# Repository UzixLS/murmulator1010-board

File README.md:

## Murmulator.1010
10×10 cm, 2-layer DIY computer PCB based on the Raspberry Pi RP2350 MCU

Technical specs:
- Compatible with the [Murmulator](https://murmulator.ru/) [M2P2](https://murmulator.ru/nextgen)
  and [Frank PGA](https://frank.rh1.tech/ru-ru/hardware/frank-pga) projects
- HDMI and VGA video outputs
- CVBS composite video + audio output via 3.5mm jack connector
- PWM and I2S (TDA1387T DAC) audio output with LMV358 opamp
- Combined PS/2 keyboard and mouse port
- Two DB-9 ports for Famicom (Dendy)-compatible joysticks
- Two external USB-host ports and two internal connectors via an MW7211A hub
- USB Type-C power supply and programming
- RP2350B MCU in a QFN-80 package
- 16MB SPI flash (W25Q128)
- Two PSRAM chips: SPI + QSPI
- RTC (DS3231MZ) with battery
- ESP8266 WiFi module (ESP-01 or ESP-12E/F)
- SD/microSD card slot
- Tape input via a second 3.5 mm jack
- ESD protection for PS/2, joystick, and USB Type-C ports
- 5V level shifters for PS/2 and joystick ports
- Board optimized for G738 and G706 cases

### Navigation
[release/pcb.rev.A1.pdf](https://uzixls.github.io/murmulator1010-board/release/pcb.rev.A1.pdf) - schematic, BOM and 3d renders  
[release/pcb.rev.A1.bom_interactive.html](https://uzixls.github.io/murmulator1010-board/release/pcb.rev.A1.bom_interactive.html) - interactive BOM  
[release/pcb.rev.A1.gerber.zip](https://uzixls.github.io/murmulator1010-board/release/pcb.rev.A1.gerber.zip) - gerber files  
[release/pcb_covers.rev.A1.gerber.zip](https://uzixls.github.io/murmulator1010-board/release/pcb_covers.rev.A1.gerber.zip) - gerber files for covers  

### Changelog
#### Main PCB
* Rev.A - initial release
* Rev.A1:
    - U6 marked as DNP
    - Minor silkscreen improvements

#### Covers PCB
* Rev.A - initial release
* Rev.A1:
    - HDMI and USB cutouts moved down by 0.25mm
    - PS/2 cutout moved up by 0.25mm

### MCU pinout
| GPIO | Function |
| ---- | -------- |
| GP0  | PS/2 mouse clock |
| GP1  | PS/2 mouse data |
| GP2  | PS/2 keyboard clock |
| GP3  | PS/2 keyboard data |
| GP4  | SPI SD card and PSRAM MISO |
| GP5  | SPI SD card select |
| GP6  | SPI SD card and PSRAM clock |
| GP7  | SPI SD card and PSRAM MOSI |
| GP8  | SPI PSRAM select |
| GP9  | I2S data / PWM beeper |
| GP10 | I2S clock / PWM R |
| GP11 | I2S LR clock / PWM L |
| GP12 | HDMI CKN / VGA B bit 0 / CVBS bit 0 |
| GP13 | HDMI CKP / VGA B bit 1 / CVBS bit 1 |
| GP14 | HDMI D0N / VGA G bit 0 / CVBS bit 4 |
| GP15 | HDMI D0P / VGA G bit 1 / CVBS bit 5 |
| GP16 | HDMI D1N / VGA R bit 0 / CVBS bit 2 |
| GP17 | HDMI D1P / VGA R bit 1 / CVBS bit 3 |
| GP18 | HDMI D2N / VGA horizontal sync / CVBS bit 6 |
| GP19 | HDMI D2P / VGA vertical sync |
| GP20 | NES joystick 1+2 clock |
| GP21 | NES joystick 1+2 latch |
| GP22 | Tape input |
| GP23 | — |
| GP24 | User button |
| GP25 | User LED |
| GP26 | NES joystick 1 data |
| GP27 | NES joystick 2 data |
| GP28 | RTC I2C SDA |
| GP29 | RTC I2C SCL |
| GP30 | — |
| GP31 | Test point TP4 |
| GP32 | Test point TP5 |
| GP33 | Test point TP6 |
| GP34 | — |
| GP35 | — |
| GP36 | — |
| GP37 | — |
| GP38 | ESP UART RX (MCU output) |
| GP39 | ESP UART TX (MCU input) |
| GP40 | — |
| GP41 | — |
| GP42 | — |
| GP43 | — |
| GP44 | — |
| GP45 | — |
| GP46 | Test point TP7 |
| GP47 | QSPI PSRAM select |

### References
* Murmulator official site: [link](https://murmulator.ru/)
* Murmulator 2 pinout and firmware: [link](https://murmulator.ru/nextgen)
* Frank PGA: [link](https://frank.rh1.tech/ru-ru/hardware/frank-pga)

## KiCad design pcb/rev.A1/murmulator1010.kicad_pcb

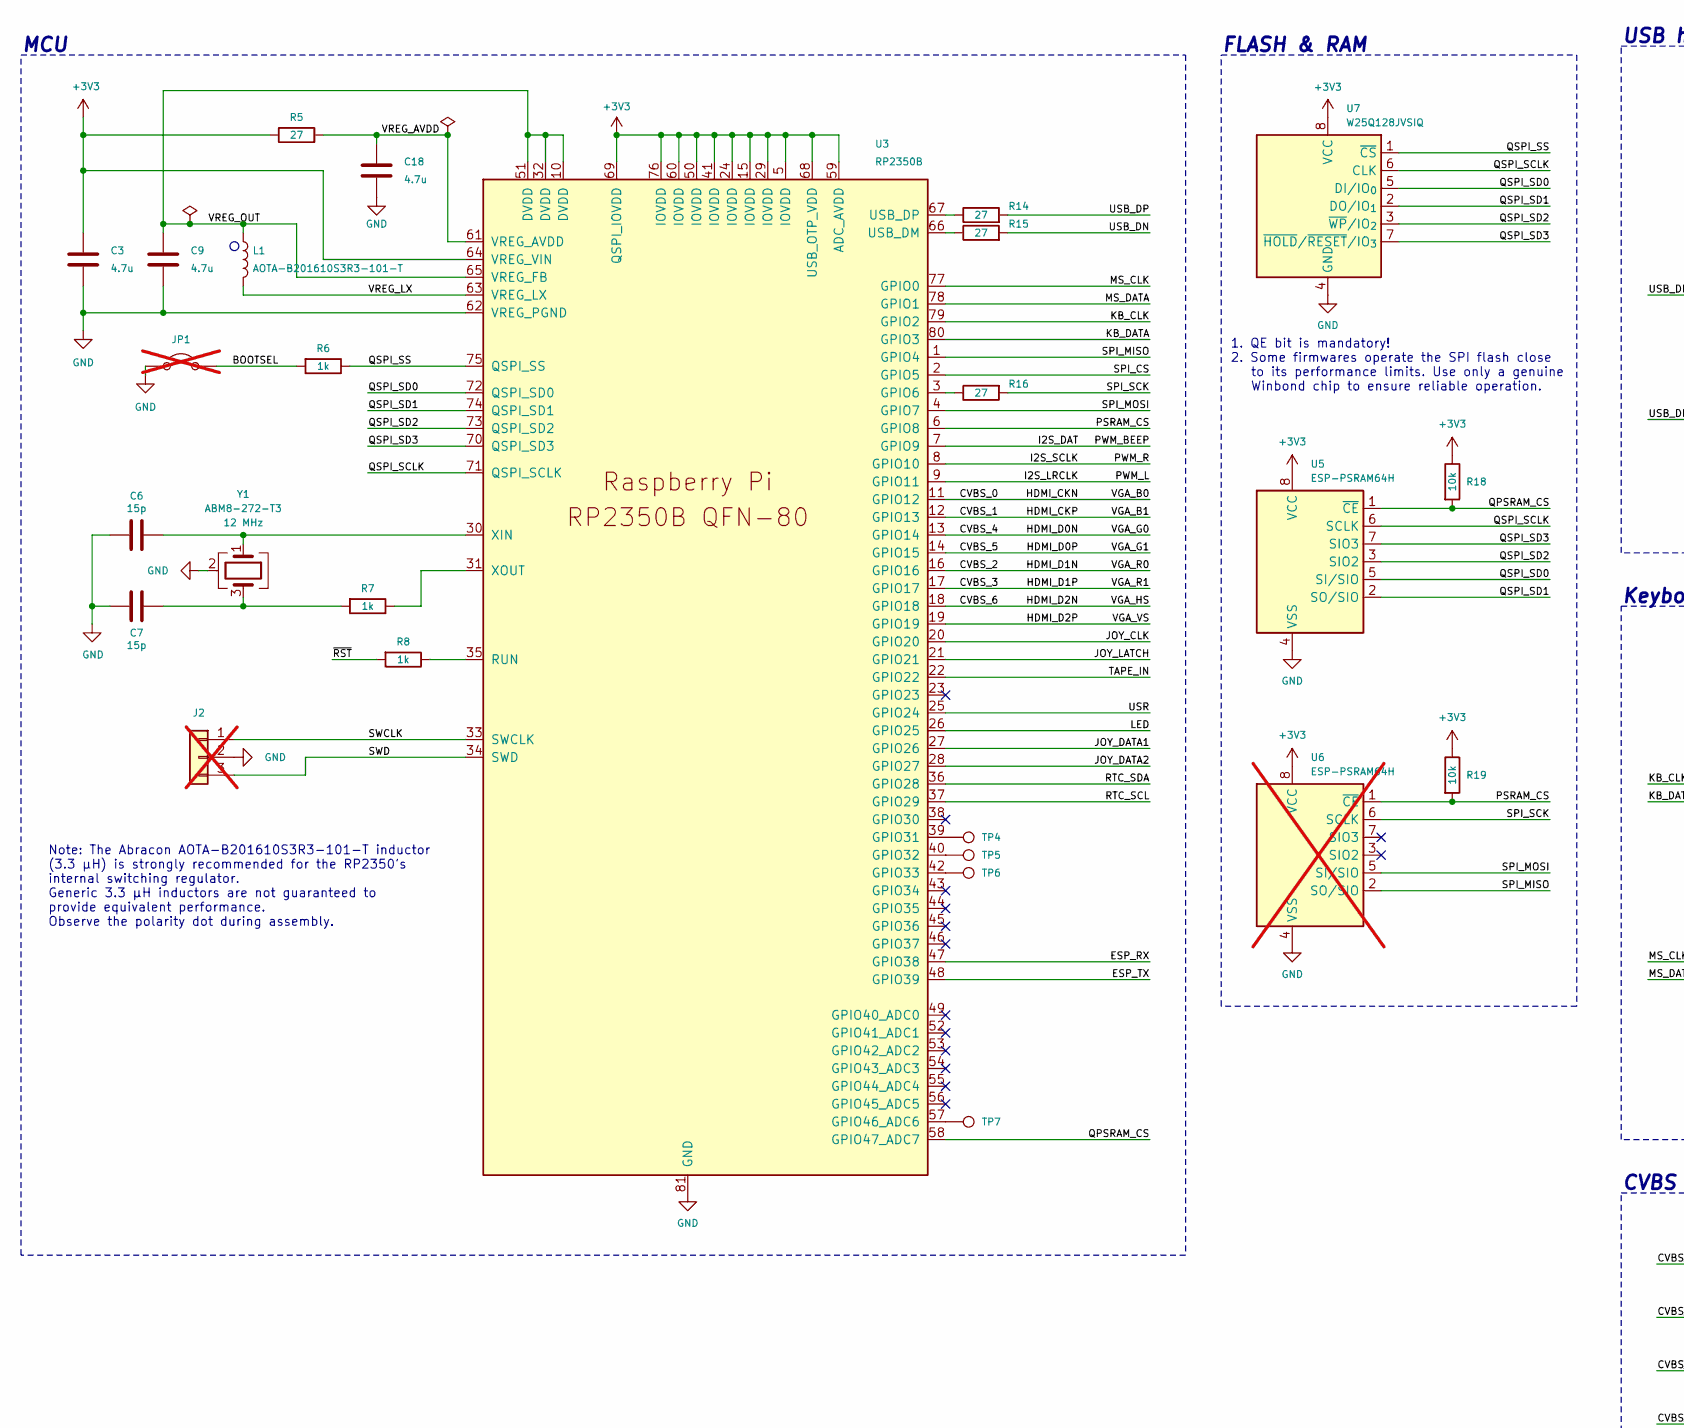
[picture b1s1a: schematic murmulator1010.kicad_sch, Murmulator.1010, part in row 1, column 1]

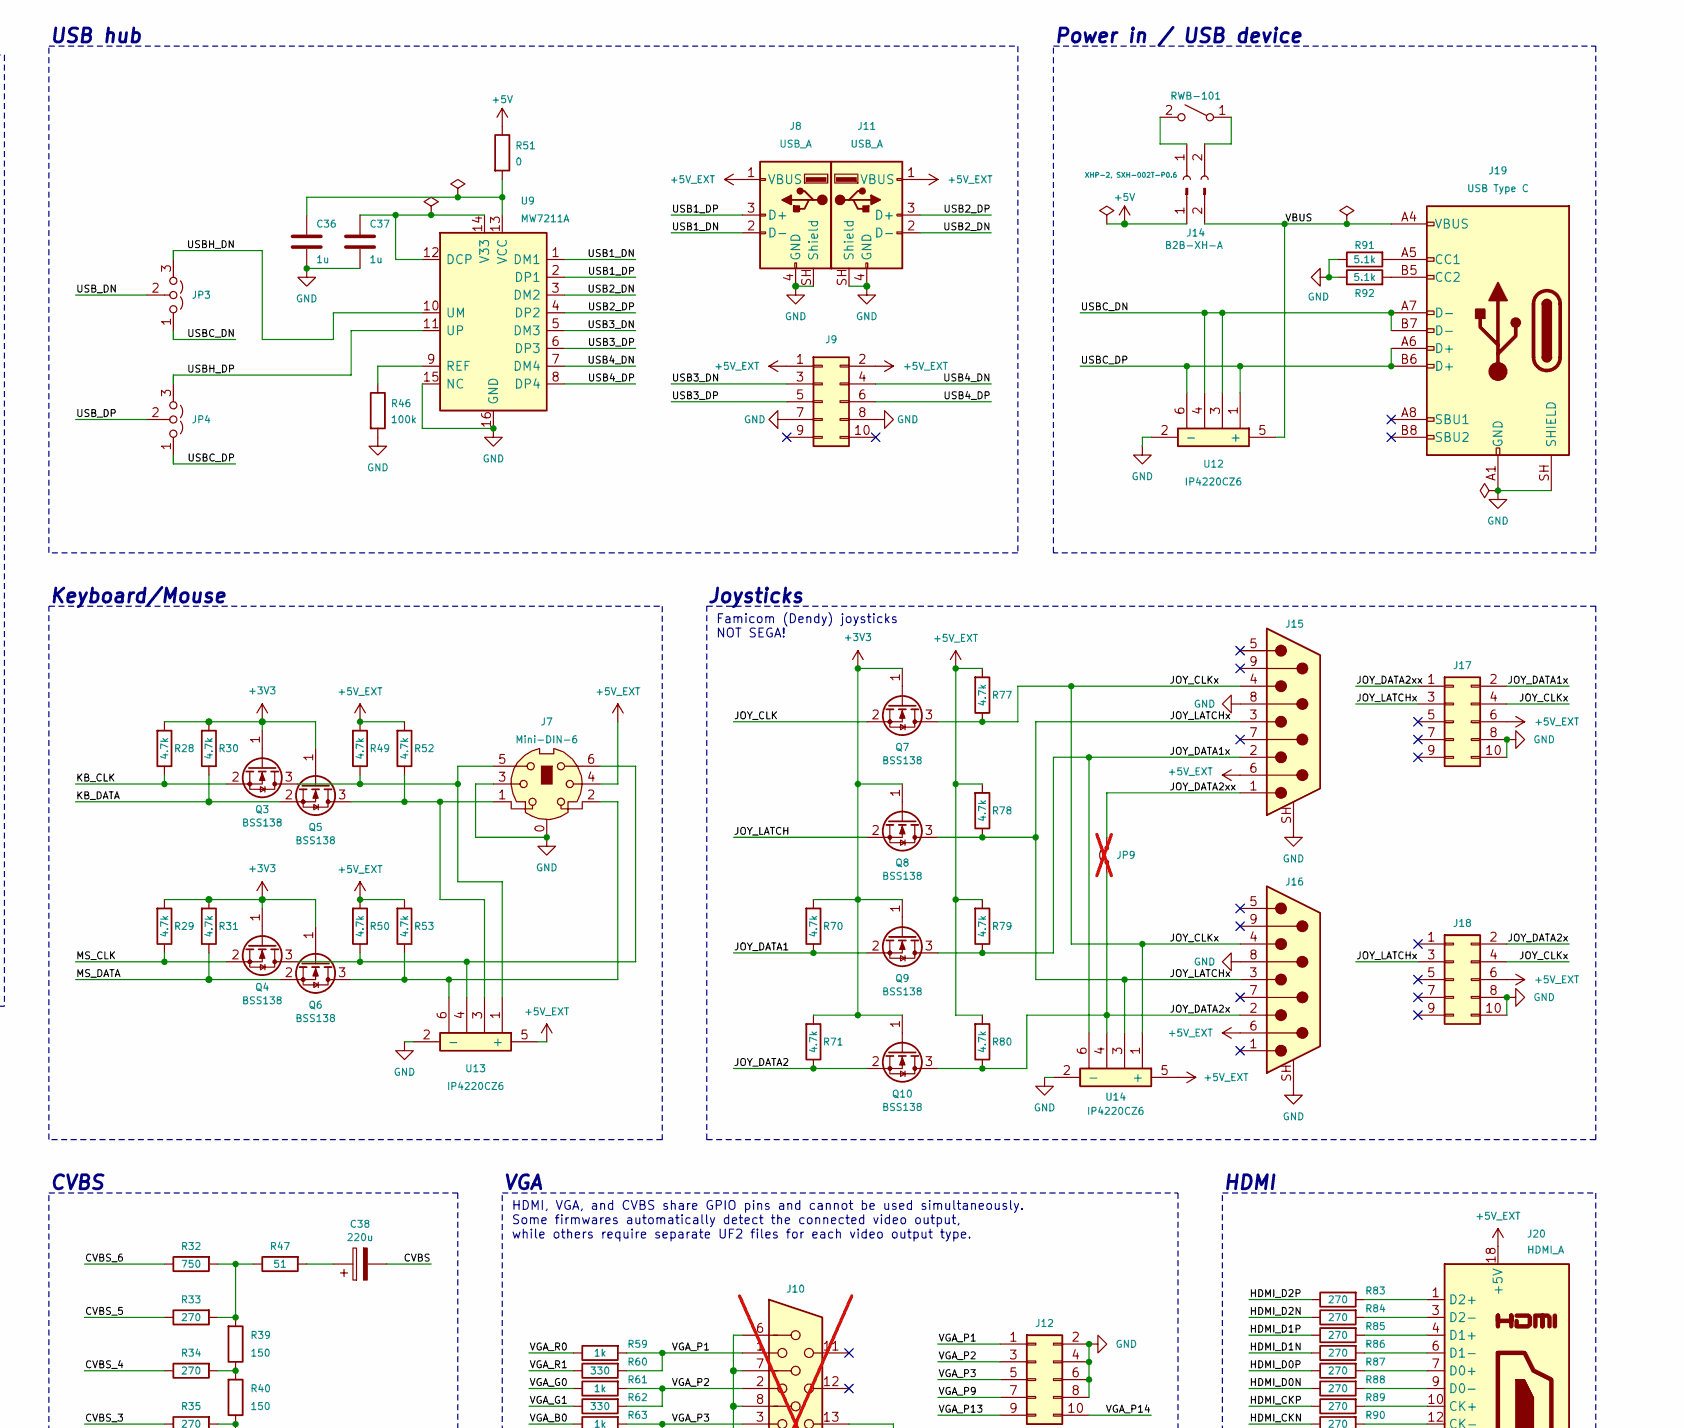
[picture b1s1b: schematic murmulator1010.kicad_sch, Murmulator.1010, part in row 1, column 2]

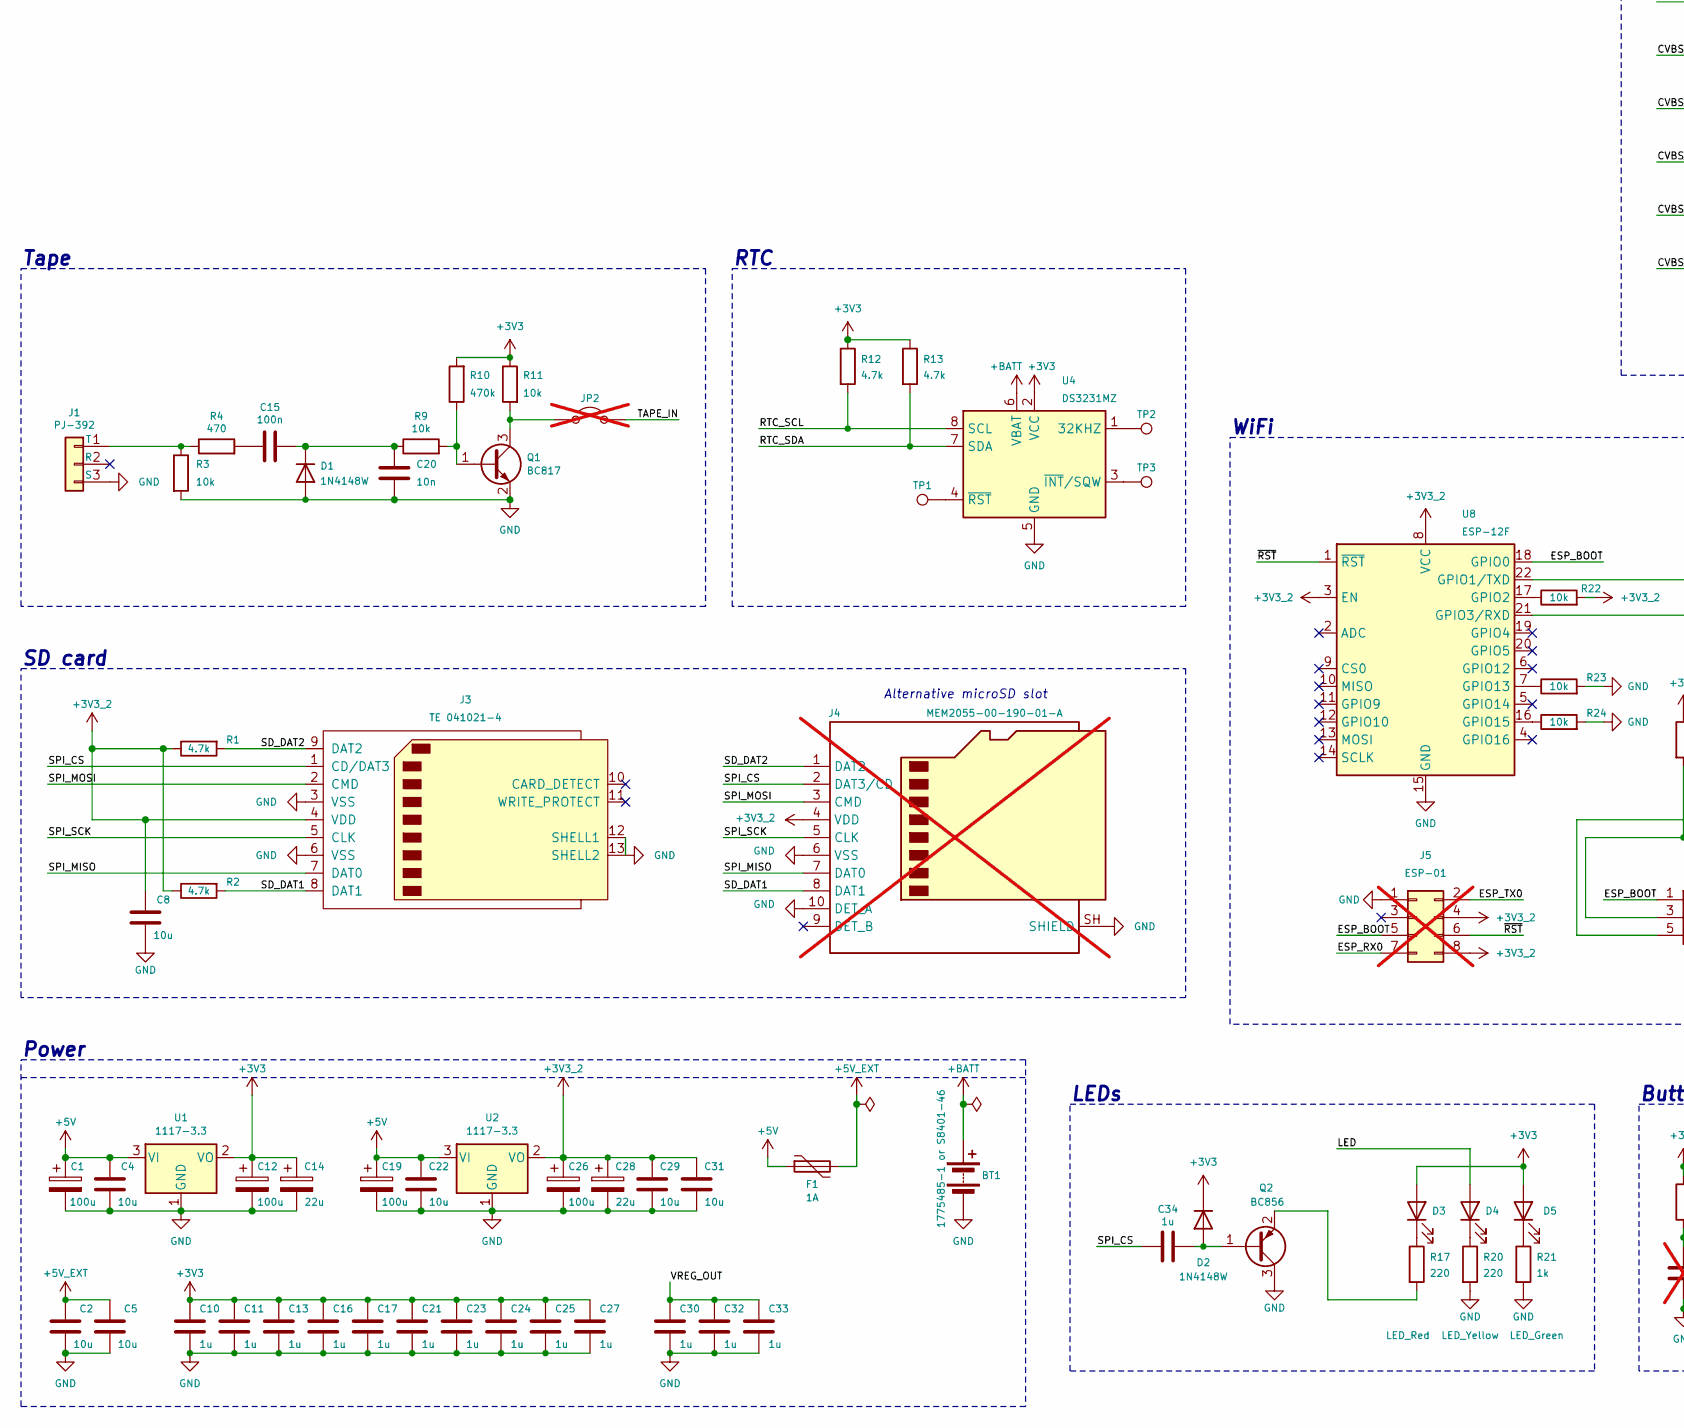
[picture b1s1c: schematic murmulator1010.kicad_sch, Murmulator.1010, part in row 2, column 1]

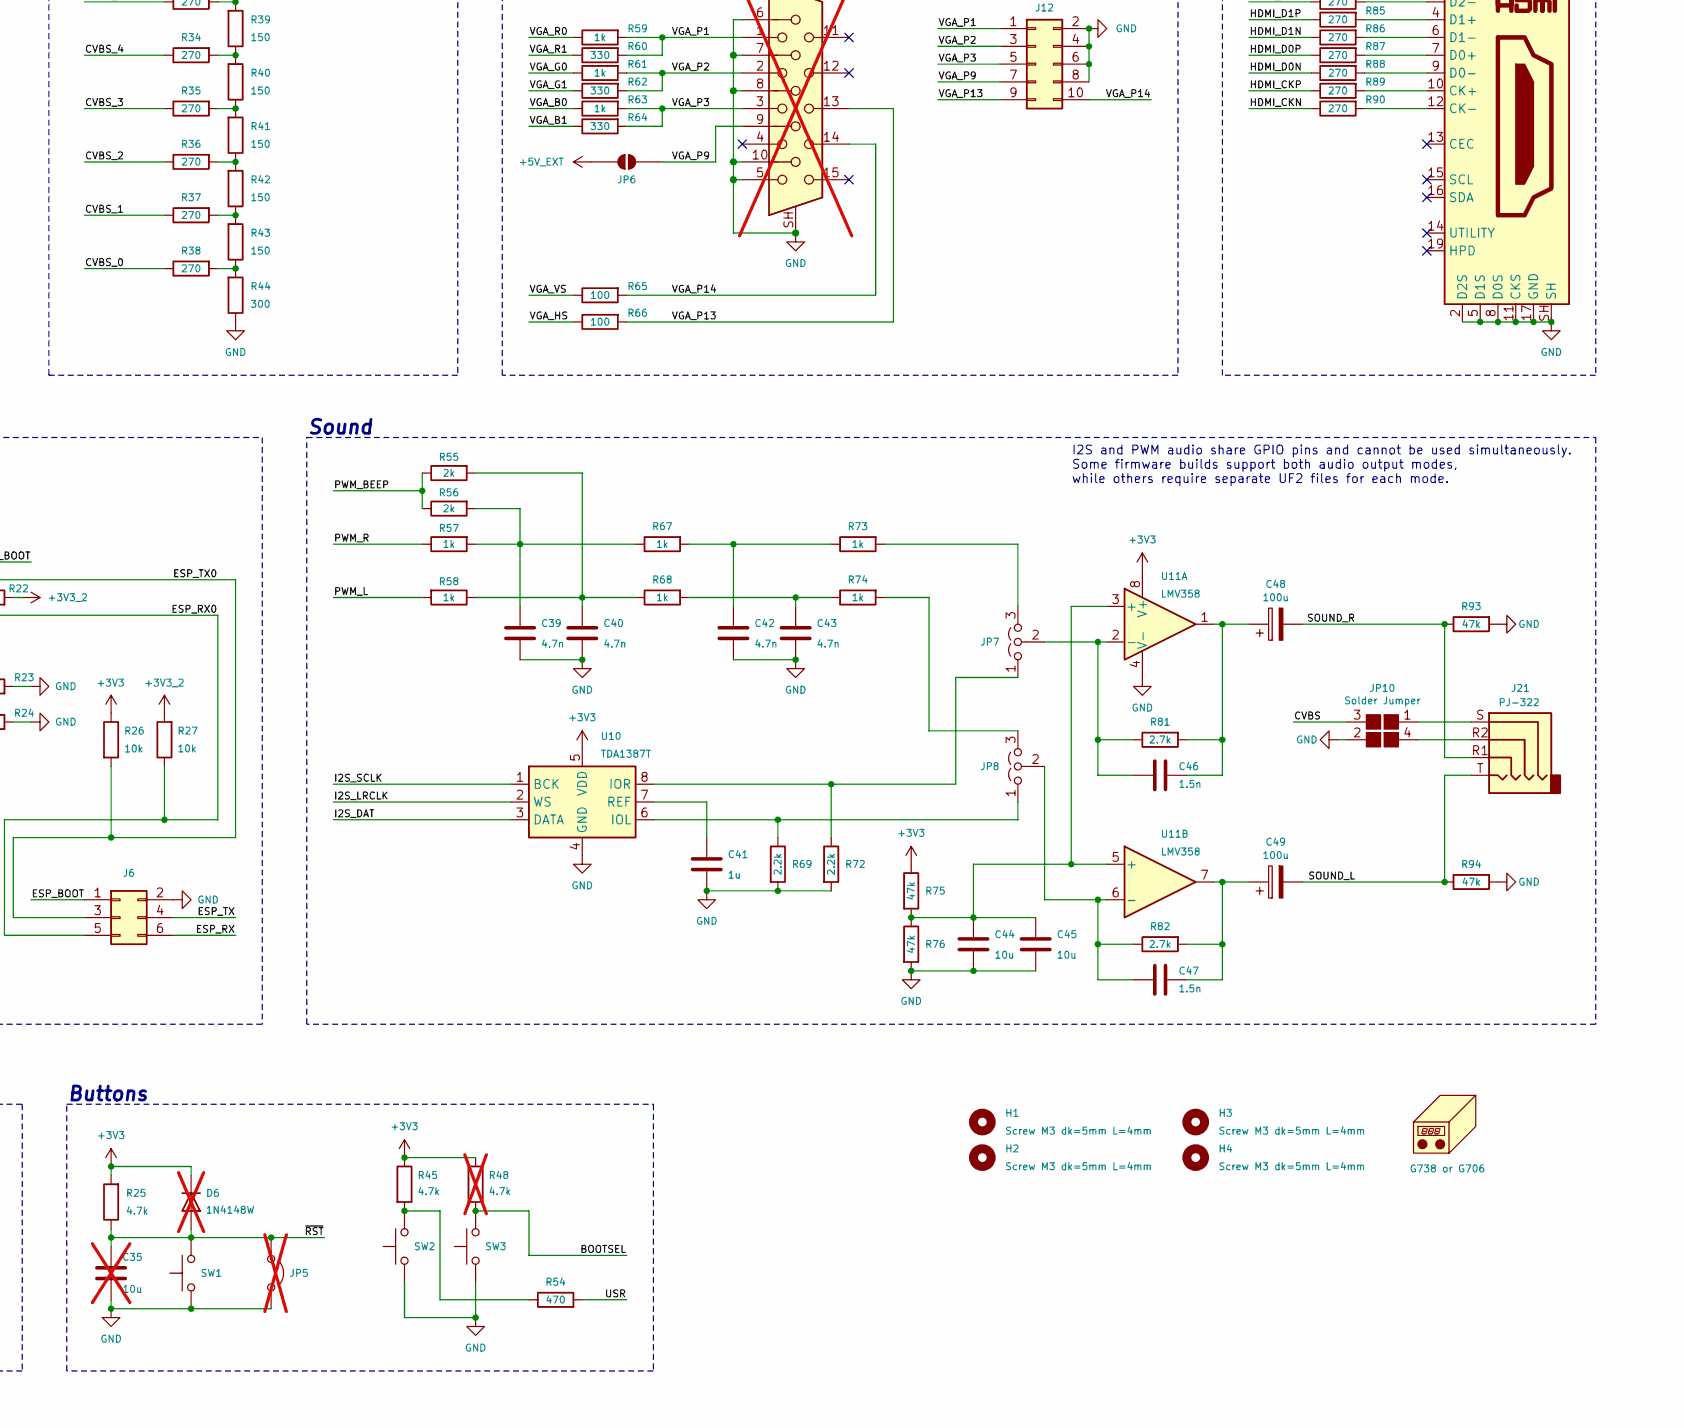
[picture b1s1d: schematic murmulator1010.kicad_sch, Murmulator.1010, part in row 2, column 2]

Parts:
BT1: 1775485-1 or S8401-46; CR2032V
C1, C12, C19, C26, C48, C49: 100u; CP_Elec_5x5.9
C2, C4, C5, C8, C22, C29, C31, C44, C45: 10u; C_0805_2012Metric_Pad1.18x1.45mm_HandSolder
C3, C9, C18: 4.7u; C_0805_2012Metric_Pad1.18x1.45mm_HandSolder
C6, C7: 15p; C_0805_2012Metric_Pad1.18x1.45mm_HandSolder
C10, C11, C13, C16, C17, C21, C23, C24, C25, C27, C30, C32, C33, C34, C36, C37, C41: 1u; C_0805_2012Metric_Pad1.18x1.45mm_HandSolder
C14, C28: 22u; CP_EIA-3216-18_Kemet-A_HandSolder
C15: 100n; C_0805_2012Metric_Pad1.18x1.45mm_HandSolder
C20: 10n; C_0805_2012Metric_Pad1.18x1.45mm_HandSolder
C35: 10u; C_0805_2012Metric_Pad1.18x1.45mm_HandSolder; not fitted
C38: 220u; CP_Elec_6.3x7.7
C39, C40, C42, C43: 4.7n; C_0805_2012Metric_Pad1.18x1.45mm_HandSolder
C46, C47: 1.5n; C_0805_2012Metric_Pad1.18x1.45mm_HandSolder
D1, D2: 1N4148W; D_SOD-123
D3: LED_Red; LED_D5.0mm_Horizontal_O1.27mm_Z3.0mm
D4: LED_Yellow; LED_D5.0mm_Horizontal_O1.27mm_Z3.0mm
D5: LED_Green; LED_D5.0mm_Horizontal_O1.27mm_Z3.0mm
D6: 1N4148W; D_SOD-123; not fitted
F1: 1A; Fuse_1812_4532Metric_Pad1.30x3.40mm_HandSolder
H1, H2, H3, H4: Screw M3 dk=5mm L=4mm; MountingHole_3.2mm_M3_dk5.2mm_Mask
J1: PJ-392; PinHeader_1x03_P2.54mm_Vertical
J2: Conn_01x03; PinHeader_1x03_P2.54mm_Vertical; not fitted
J3: TE 041021-4; SD_TE_2041021-mod
J4: MEM2055-00-190-01-A; microSD_GCT-MEM2055-00-190-01-A; not fitted
J5: ESP-01; PinSocket_2x04_P2.54mm_Vertical; not fitted
J6: Conn_02x03_Odd_Even; PinHeader_2x03_P2.54mm_Vertical
J7: Mini-DIN-6; minidin-6
J8, J11: USB_A; USB_A_Wuerth_614004134726_Horizontal
J9, J12, J17, J18: Conn_02x05_Odd_Even; PinHeader_2x05_P2.54mm_Vertical
J10: DB15_Female_HighDensity_MountingHoles; DSUB-15-HD_Female_Horizontal_P2.29x1.98mm_EdgePinOffset3.03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; not fitted
J13: XHP-2, SXH-002T-P0.6
J14: B2B-XH-A; JST_XH_B2B-XH-A_1x02_P2.50mm_Vertical
J15, J16: DB9-M; DSUB-9_Pins_Horizontal_P2.77x2.84mm_EdgePinOffset7.70mm_Hou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
J19: USB Type C; USB_C_Receptacle_HRO_TYPE-C-31-M-12_dangling
J20: HDMI_A; HDMI_A_Molex_208658-1001_Horizontal
J21: PJ-322
JP1, JP2: Jumper_2_Open; PinHeader_1x02_P2.54mm_Vertical; not fitted
JP3, JP4, JP7, JP8: Jumper_3_Open; PinHeader_1x03_P2.54mm_Vertical
JP5, JP9: Jumper_2_Small_Open; PinHeader_1x02_P2.54mm_Vertical; not fitted
JP6: SolderJumper_2_Open; SolderJumper-2_P1.3mm_Open_RoundedPad1.0x1.5mm
JP10: Solder Jumper; SolderJumper-4_P1.3mm_Open
L1: AOTA-B201610S3R3-101-T; L_1008_2520Metric
N1: G738 or G706; g738-g706
Q1: BC817; SOT-23
Q2: BC856; SOT-23
Q3, Q4, Q5, Q6, Q7, Q8, Q9, Q10: BSS138; SOT-23
R1, R2, R12, R13, R25, R28, R29, R30, R31, R45, R49, R50, R52, R53, R70, R71, R77, R78, R79, R80: 4.7k; R_0805_2012Metric_Pad1.20x1.40mm_HandSolder
R3, R9, R11, R18, R19, R22, R23, R24, R26, R27: 10k; R_0805_2012Metric_Pad1.20x1.40mm_HandSolder
R4, R54: 470; R_0805_2012Metric_Pad1.20x1.40mm_HandSolder
R5, R14, R15, R16: 27; R_0805_2012Metric_Pad1.20x1.40mm_HandSolder
R6, R7, R8, R21, R57, R58, R59, R61, R63, R67, R68, R73, R74: 1k; R_0805_2012Metric_Pad1.20x1.40mm_HandSolder
R10: 470k; R_0805_2012Metric_Pad1.20x1.40mm_HandSolder
R17, R20: 220; R_0805_2012Metric_Pad1.20x1.40mm_HandSolder
R32: 750; R_0805_2012Metric_Pad1.20x1.40mm_HandSolder
R33, R34, R35, R36, R37, R38, R83, R84, R85, R86, R87, R88, R89, R90: 270; R_0805_2012Metric_Pad1.20x1.40mm_HandSolder
R39, R40, R41, R42, R43: 150; R_0805_2012Metric_Pad1.20x1.40mm_HandSolder
R44: 300; R_0805_2012Metric_Pad1.20x1.40mm_HandSolder
R46: 100k; R_0805_2012Metric_Pad1.20x1.40mm_HandSolder
R47: 51; R_0805_2012Metric_Pad1.20x1.40mm_HandSolder
R48: 4.7k; R_0805_2012Metric_Pad1.20x1.40mm_HandSolder; not fitted
R51: 0; R_0805_2012Metric_Pad1.20x1.40mm_HandSolder
R55, R56: 2k; R_0805_2012Metric_Pad1.20x1.40mm_HandSolder
R60, R62, R64: 330; R_0805_2012Metric_Pad1.20x1.40mm_HandSolder
R65, R66: 100; R_0805_2012Metric_Pad1.20x1.40mm_HandSolder
R69, R72: 2.2k; R_0805_2012Metric_Pad1.20x1.40mm_HandSolder
R75, R76, R93, R94: 47k; R_0805_2012Metric_Pad1.20x1.40mm_HandSolder
R81, R82: 2.7k; R_0805_2012Metric_Pad1.20x1.40mm_HandSolder
R91, R92: 5.1k; R_0805_2012Metric_Pad1.20x1.40mm_HandSolder
SW1, SW2, SW3: Push angle button, 6x6x7mm or 6x6x8mm; SW_Tactile_SPST_Angled_PTS645Vx58-2LFS
SW4: RWB-101
TP1, TP2, TP3, TP4, TP5, TP6, TP7: TestPoint; TestPoint_Pad_D1.0mm
U1, U2: 1117-3.3; SOT-223-3_TabPin2
U3: RP2350B; QFN-80-1EP_10x10mm_P0.4mm_EP3.4x3.4mm
U4: DS3231MZ; SOIC-8_3.9x4.9mm_P1.27mm
U5: ESP-PSRAM64H; SOIC-8_3.9x4.9mm_P1.27mm
U6: ESP-PSRAM64H; SOIC-8_3.9x4.9mm_P1.27mm; not fitted
U7: W25Q128JVSIQ; SOIC-8_5.3x5.3mm_P1.27mm
U8: ESP-12F; ESP-12E
U9: MW7211A; SOP-16_4.4x10.4mm_P1.27mm
U10: TDA1387T; SO-8_3.9x4.9mm_P1.27mm
U11: LMV358; SOIC-8_3.9x4.9mm_P1.27mm
U12, U13, U14: IP4220CZ6; SC-74-6_1.55x2.9mm_P0.95mm
Y1: ABM8-272-T3; Crystal_SMD_3225-4Pin_3.2x2.5mm_HandSoldering

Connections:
+3V3: C3.1, C10.2, C11.2, C12.1, C13.2, C14.1, C16.2, C17.2, C21.2, C23.2, C24.2, C25.2, C27.2, D2.1 (K), D3.2 (A), D5.2 (A), D6.1 (K), Q3.1 (G), Q4.1 (G), Q5.1 (G), Q6.1 (G), Q7.1 (G), Q8.1 (G), Q9.1 (G), Q10.1 (G), R5.1, R10.2, R11.1, R12.1, R13.1, R18.1, R19.1, R25.2, R26.1, R28.2, R29.2, R30.2, R31.2, R45.1, R48.1, R70.2, R71.2, R75.1, U1.2 (VO), U3.5 (IOVDD), U3.15 (IOVDD), U3.24 (IOVDD), U3.29 (IOVDD), U3.41 (IOVDD), U3.50 (IOVDD), U3.59 (ADC_AVDD), U3.60 (IOVDD), U3.64 (VREG_VIN), U3.68 (USB_OTP_VDD), U3.69 (QSPI_IOVDD), U3.76 (IOVDD), U4.2 (VCC), U5.8 (VCC), U6.8 (VCC), U7.8 (VCC), U10.5 (VDD), U11.8 (V+)
+3V3_2: C8.2, C26.1, C28.1, C29.2, C31.2, J3.4 (VDD), J4.4 (VDD), J5.4, J5.8, R1.1, R2.1, R22.2, R27.2, U2.2 (VO), U8.3 (EN), U8.8 (VCC)
+5V: C1.1, C4.2, C19.1, C22.2, F1.1, J14.1, R51.1, U1.3 (VI), U2.3 (VI)
+5V_EXT: C2.2, C5.2, F1.2, J7.4, J8.1 (VBUS), J9.1, J9.2, J11.1 (VBUS), J15.6, J16.6, J17.6, J18.6, J20.18 (+5V), JP6.2 (B), R49.2, R50.2, R52.2, R53.2, R77.2, R78.2, R79.2, R80.2, U13.5 (+), U14.5 (+)
+BATT: BT1.1 (+), U4.6 (VBAT)
/BOOTSEL: JP1.1 (A), R6.2, R48.2, SW3.1
/CVBS: C38.2, JP10.3
/CVBS_0: R38.1, R63.1, R90.1, U3.11 (GPIO12)
/CVBS_1: R37.1, R64.1, R89.1, U3.12 (GPIO13)
/CVBS_2: R36.1, R59.1, R86.1, U3.16 (GPIO16)
/CVBS_3: R35.1, R60.1, R85.1, U3.17 (GPIO17)
/CVBS_4: R34.1, R61.1, R88.1, U3.13 (GPIO14)
/CVBS_5: R33.1, R62.1, R87.1, U3.14 (GPIO15)
/CVBS_6: R32.1, R66.1, R84.1, U3.18 (GPIO18)
/ESP_BOOT: J5.5, J6.1, U8.18 (GPIO0)
/ESP_RX: J6.6, U3.47 (GPIO38)
/ESP_RX0: J5.7, J6.5, R27.1, U8.21 (GPIO3/RXD)
/ESP_TX: J6.4, U3.48 (GPIO39)
/ESP_TX0: J5.2, J6.3, R26.2, U8.22 (GPIO1/TXD)
/HDMI_D2P: R65.1, R83.1, U3.19 (GPIO19)
/I2S_DAT: R55.1, R56.1, U3.7 (GPIO9), U10.3 (DATA)
/I2S_LRCLK: R58.2, U3.9 (GPIO11), U10.2 (WS)
/I2S_SCLK: R57.1, U3.8 (GPIO10), U10.1 (BCK)
/JOY_CLK: Q7.2 (S), U3.20 (GPIO20)
/JOY_CLKx: J15.4, J16.4, J17.4, J18.4, Q7.3 (D), R77.1, U14.1
/JOY_DATA1: Q9.2 (S), R70.1, U3.27 (GPIO26)
/JOY_DATA1x: J15.2, J17.2, Q9.3 (D), R79.1, U14.6
/JOY_DATA2: Q10.2 (S), R71.1, U3.28 (GPIO27)
/JOY_DATA2x: J16.2, J18.2, JP9.2 (B), Q10.3 (D), R80.1, U14.4
/JOY_DATA2xx: J15.1, J17.1, JP9.1 (A)
/JOY_LATCH: Q8.2 (S), U3.21 (GPIO21)
/JOY_LATCHx: J15.3, J16.3, J17.3, J18.3, Q8.3 (D), R78.1, U14.3
/KB_CLK: Q3.2 (S), R28.1, U3.79 (GPIO2)
/KB_DATA: Q5.2 (S), R30.1, U3.80 (GPIO3)
/LED: D4.2 (A), U3.26 (GPIO25)
/MS_CLK: Q4.2 (S), R29.1, U3.77 (GPIO0)
/MS_DATA: Q6.2 (S), R31.1, U3.78 (GPIO1)
/PSRAM_CS: R19.2, U3.6 (GPIO8), U6.1 (~CE)
/QPSRAM_CS: R18.2, U3.58 (GPIO47_ADC7), U5.1 (~CE)
/QSPI_SCLK: U3.71 (QSPI_SCLK), U5.6 (SCLK), U7.6 (CLK)
/QSPI_SD0: U3.72 (QSPI_SD0), U5.5 (SI/SIO), U7.5 (DI/IO_{0})
/QSPI_SD1: U3.74 (QSPI_SD1), U5.2 (SO/SIO), U7.2 (DO/IO_{1})
/QSPI_SD2: U3.73 (QSPI_SD2), U5.3 (SIO2), U7.3 (~WP/IO_{2})
/QSPI_SD3: U3.70 (QSPI_SD3), U5.7 (SIO3), U7.7 (~HOLD/~RESET/IO_{3})
/QSPI_SS: R6.1, U3.75 (QSPI_SS), U7.1 (~CS)
/RTC_SCL: R12.2, U3.37 (GPIO29), U4.8 (SCL)
/RTC_SDA: R13.2, U3.36 (GPIO28), U4.7 (SDA)
/SD_DAT1: J3.8 (DAT1), J4.8 (DAT1), R2.2
/SD_DAT2: J3.9 (DAT2), J4.1 (DAT2), R1.2
/SOUND_L: C49.2, J21.T, R94.1
/SOUND_R: C48.2, J21.R1, R93.1
/SPI_CS: C34.1, J3.1 (CD/DAT3), J4.2 (DAT3/CD), U3.2 (GPIO5)
/SPI_MISO: J3.7 (DAT0), J4.7 (DAT0), U3.1 (GPIO4), U6.2 (SO/SIO)
/SPI_MOSI: J3.2 (CMD), J4.3 (CMD), U3.4 (GPIO7), U6.5 (SI/SIO)
/SPI_SCK: J3.5 (CLK), J4.5 (CLK), R16.2, U6.6 (SCLK)
/SWCLK: J2.1, U3.33 (SWCLK)
/SWD: J2.3, U3.34 (SWD)
/TAPE_IN: JP2.1 (A), U3.22 (GPIO22)
/USB1_DN: J8.2 (D-), U9.1 (DM1)
/USB1_DP: J8.3 (D+), U9.2 (DP1)
/USB2_DN: J11.2 (D-), U9.3 (DM2)
/USB2_DP: J11.3 (D+), U9.4 (DP2)
/USB3_DN: J9.3, U9.5 (DM3)
/USB3_DP: J9.5, U9.6 (DP3)
/USB4_DN: J9.4, U9.7 (DM4)
/USB4_DP: J9.6, U9.8 (DP4)
/USBC_DN: J19.A7 (D-), J19.B7 (D-), JP3.1 (A), U12.3, U12.4
/USBC_DP: J19.A6 (D+), J19.B6 (D+), JP4.1 (A), U12.1, U12.6
/USBH_DN: JP3.3 (B), U9.10 (UM)
/USBH_DP: JP4.3 (B), U9.11 (UP)
/USB_DN: JP3.2 (C), R15.2
/USB_DP: JP4.2 (C), R14.2
/USR: R54.2, U3.25 (GPIO24)
/VBUS: J14.2, J19.A4 (VBUS), J19.A9 (VBUS), J19.B4 (VBUS), J19.B9 (VBUS), U12.5 (+)
/VGA_P1: J10.1, J12.1, R59.2, R60.2
/VGA_P2: J10.2, J12.3, R61.2, R62.2
/VGA_P3: J10.3, J12.5, R63.2, R64.2
/VGA_P9: J10.9, J12.7, JP6.1 (A)
/VGA_P13: J10.13, J12.9, R66.2
/VGA_P14: J10.14, J12.10, R65.2
/VREG_AVDD: C18.1, R5.2, U3.61 (VREG_AVDD)
/VREG_LX: L1.2, U3.63 (VREG_LX)
/VREG_OUT: C9.1, C30.2, C32.2, C33.2, L1.1, U3.10 (DVDD), U3.32 (DVDD), U3.51 (DVDD), U3.65 (VREG_FB)
/~RST: C35.2, D6.2 (A), J5.6, JP5.1 (A), R8.2, R25.1, SW1.1, U8.1 (~RST)
GND: BT1.2 (-), C1.2, C2.1, C3.2, C4.1, C5.1, C6.2, C7.2, C8.1, C9.2, C10.1, C11.1, C12.2, C13.1, C14.2, C16.1, C17.1, C18.2, C19.2, C20.2, C21.1, C22.1, C23.1, C24.1, C25.1, C26.2, C27.1, C28.2, C29.1, C30.1, C31.1, C32.1, C33.1, C35.1, C36.1, C37.1, C39.2, C40.2, C41.2, C42.2, C43.2, C44.2, C45.2, D1.2 (A), J1.3, J2.2, J3.3 (VSS), J3.6 (VSS), J3.12 (SHELL1), J3.13 (SHELL2), J4.6 (VSS), J4.10 (DET_A), J4.SH (SHIELD), J5.1, J6.2, J7.0, J7.3, J8.4 (GND), J8.SH (Shield), J9.7, J9.8, J10.5, J10.6, J10.7, J10.8, J10.10, J10.SH, J11.4 (GND), J11.SH (Shield), J12.2, J12.4, J12.6, J12.8, J15.8, J15.SH (PAD), J16.8, J16.SH (PAD), J17.8, J17.10, J18.8, J18.10, J19.A1 (GND), J19.A12 (GND), J19.B1 (GND), J19.B12 (GND), J19.SH (SHIELD), J20.2 (D2S), J20.5 (D1S), J20.8 (D0S), J20.11 (CKS), J20.17 (GND), J20.SH, JP1.2 (B), JP5.2 (B), JP10.2, Q1.2 (E), Q2.3 (C), R3.2, R20.2, R21.2, R23.2, R24.2, R44.1, R46.2, R69.2, R72.2, R76.2, R91.1, R92.1, R93.2, R94.2, SW1.2, SW2.2, SW3.2, U1.1 (GND), U2.1 (GND), U3.62 (VREG_PGND), U3.81 (GND), U4.5 (GND), U5.4 (VSS), U6.4 (VSS), U7.4 (GND), U8.15 (GND), U9.15 (NC), U9.16 (GND), U10.4 (GND), U11.4 (V-), U12.2 (-), U13.2 (-), U14.2 (-), Y1.2 (G), Y1.4 (G)
unnamed: C7.1, R7.2, Y1.3
unnamed: C15.2, R4.2
unnamed: C38.1, R47.2
unnamed: C39.1, R56.2, R57.2, R67.1
unnamed: C40.1, R55.2, R58.1, R68.1
unnamed: C42.1, R67.2, R73.1
unnamed: C43.1, R68.2, R74.1
unnamed: C46.1, C48.1, R81.2, U11.1
unnamed: C47.1, C49.1, R82.2, U11.7
unnamed: C15.1, C20.1, D1.1 (K), R9.1
unnamed: C34.2, D2.2 (A), Q2.1 (B)
unnamed: D3.1 (K), R17.1
unnamed: D4.1 (K), R20.1
unnamed: D5.1 (K), R21.1
unnamed: J1.1, R3.1, R4.1
unnamed: J13.1, SW4.2 (B)
unnamed: J13.2, SW4.1 (A)
unnamed: J19.A5 (CC1), R91.2
unnamed: J19.B5 (CC2), R92.2
unnamed: J20.10 (CK+), R89.2
unnamed: J20.12 (CK-), R90.2
unnamed: J20.7 (D0+), R87.2
unnamed: J20.9 (D0-), R88.2
unnamed: J20.4 (D1+), R85.2
unnamed: J20.6 (D1-), R86.2
unnamed: J20.1 (D2+), R83.2
unnamed: J20.3 (D2-), R84.2
unnamed: J21.R2, JP10.4
unnamed: JP2.2 (B), Q1.3 (C), R11.2
unnamed: JP7.1 (A), R72.1, U10.8 (IOR)
unnamed: JP7.3 (B), R73.2
unnamed: C46.2, JP7.2 (C), R81.1, U11.2 (-)
unnamed: JP8.1 (A), R69.1, U10.6 (IOL)
unnamed: JP8.3 (B), R74.2
unnamed: C47.2, JP8.2 (C), R82.1, U11.6 (-)
unnamed: J21.S, JP10.1 (A)
unnamed: Q1.1 (B), R9.2, R10.1
unnamed: Q2.2 (E), R17.2
unnamed: J7.5, Q3.3 (D), R49.1, U13.1
unnamed: J7.6, Q4.3 (D), R50.1, U13.4
unnamed: J7.1, Q5.3 (D), R52.1, U13.3
unnamed: J7.2, Q6.3 (D), R53.1, U13.6
unnamed: R32.2, R33.2, R39.2, R47.1
unnamed: R34.2, R39.1, R40.2
unnamed: R35.2, R40.1, R41.2
unnamed: R36.2, R41.1, R42.2
unnamed: R37.2, R42.1, R43.2
unnamed: R38.2, R43.1, R44.2
unnamed: R45.2, R54.1, SW2.1
unnamed: R16.1, U3.3 (GPIO6)
unnamed: TP4.1 (1_1), U3.39 (GPIO31)
unnamed: TP5.1 (1_1), U3.40 (GPIO32)
unnamed: TP6.1 (1_1), U3.42 (GPIO33)
unnamed: TP7.1 (1_1), U3.57 (GPIO46_ADC6)
unnamed: R8.1, U3.35 (RUN)
unnamed: R15.1, U3.66 (USB_DM)
unnamed: R14.1, U3.67 (USB_DP)
unnamed: C6.1, U3.30 (XIN), Y1.1
unnamed: R7.1, U3.31 (XOUT)
unnamed: TP2.1 (1_1), U4.1 (32KHZ)
unnamed: TP3.1 (1_1), U4.3 (~INT/SQW)
unnamed: TP1.1 (1_1), U4.4 (~RST)
unnamed: R22.1, U8.17 (GPIO2)
unnamed: R23.1, U8.7 (GPIO13)
unnamed: R24.1, U8.16 (GPIO15)
unnamed: C37.2, U9.12 (DCP), U9.14 (V33)
unnamed: R46.1, U9.9 (REF)
unnamed: C36.2, R51.2, U9.13 (VCC)
unnamed: C41.1, U10.7 (REF)
unnamed: C44.1, C45.1, R75.2, R76.1, U11.3 (+), U11.5 (+)

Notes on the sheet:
Famicom (Dendy) joysticks NOT SEGA!
I2S and PWM audio share GPIO pins and cannot be used simultaneously. Some firmware builds support both audio output modes, while others require separate UF2 files for each mode.
WiFi
USB hub
Sound
FLASH & RAM
Buttons
LEDs
SD card
Note: The Abracon AOTA-B201610S3R3-101-T inductor (3.3 µH) is strongly recommended for the RP2350's internal switching regulator. Generic 3.3 µH inductors are not guaranteed to provide equivalent performance. Observe the polarity dot during assembly.
CVBS
HDMI, VGA, and CVBS share GPIO pins and cannot be used simultaneously. Some firmwares automatically detect the connected video output, while others require separate UF2 files for each video output type.
VGA
HDMI
Tape
1. QE bit is mandatory! 2. Some firmwares operate the SPI flash close to its performance limits. Use only a genuine Winbond chip to ensure reliable operation.
RTC
Joysticks
MCU
Power in / USB device
Alternative microSD slot
Power
Keyboard/Mouse

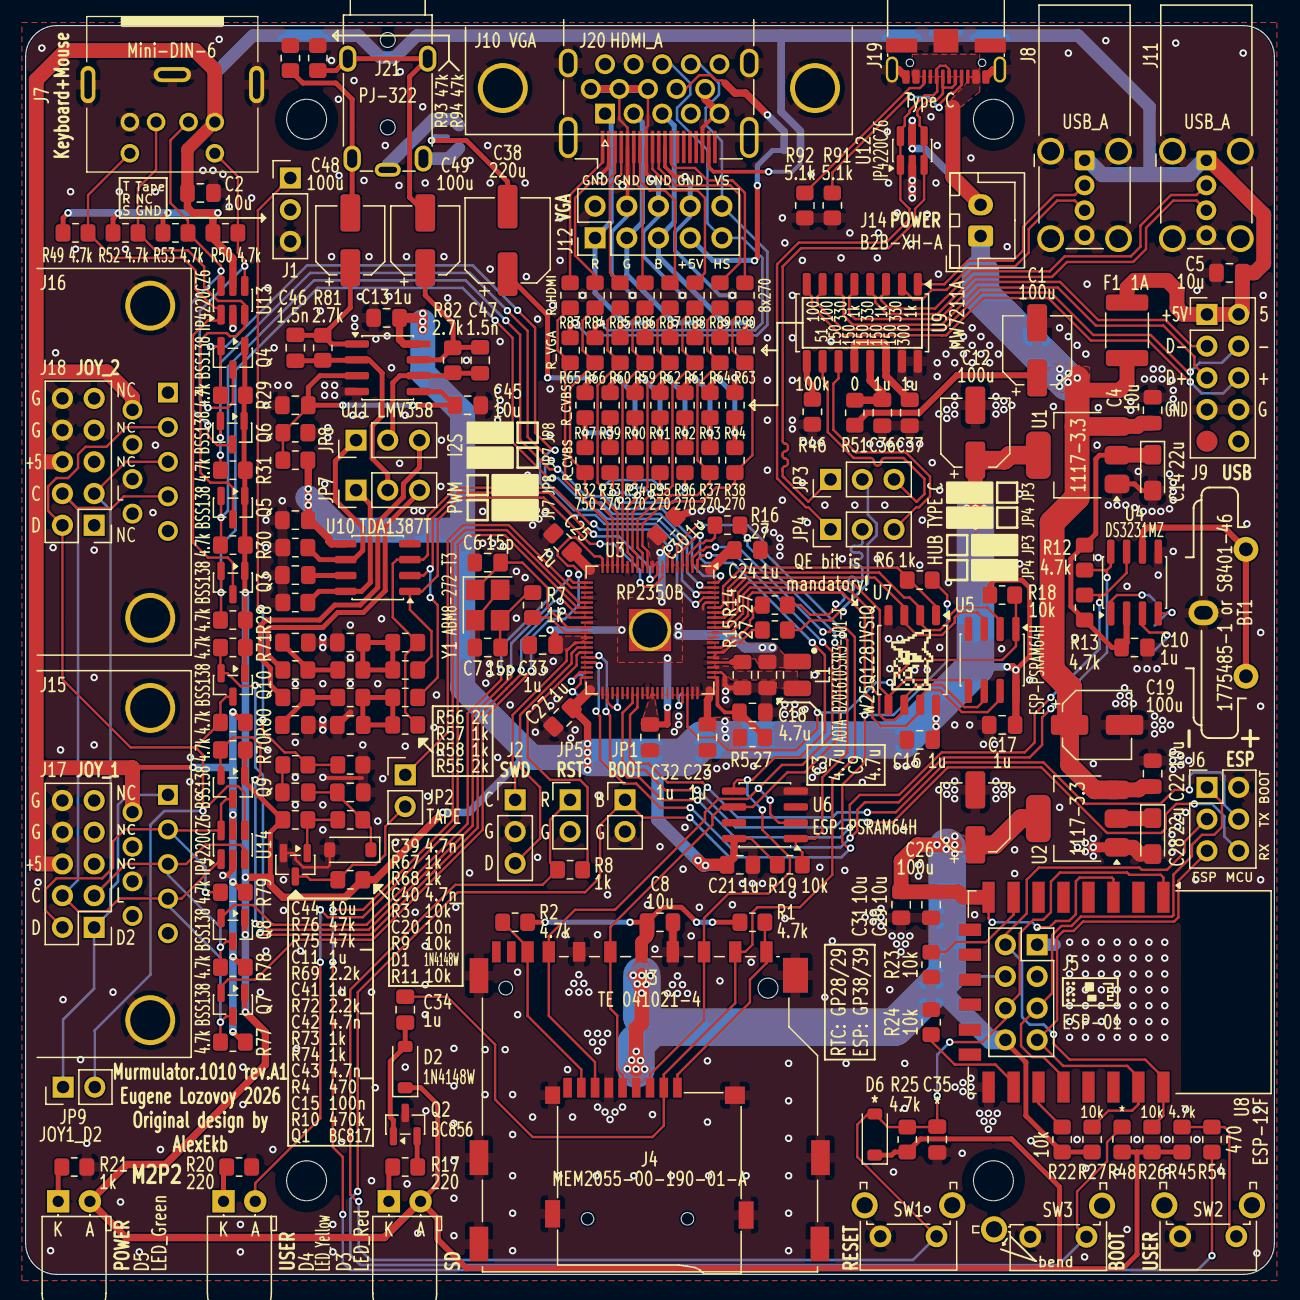
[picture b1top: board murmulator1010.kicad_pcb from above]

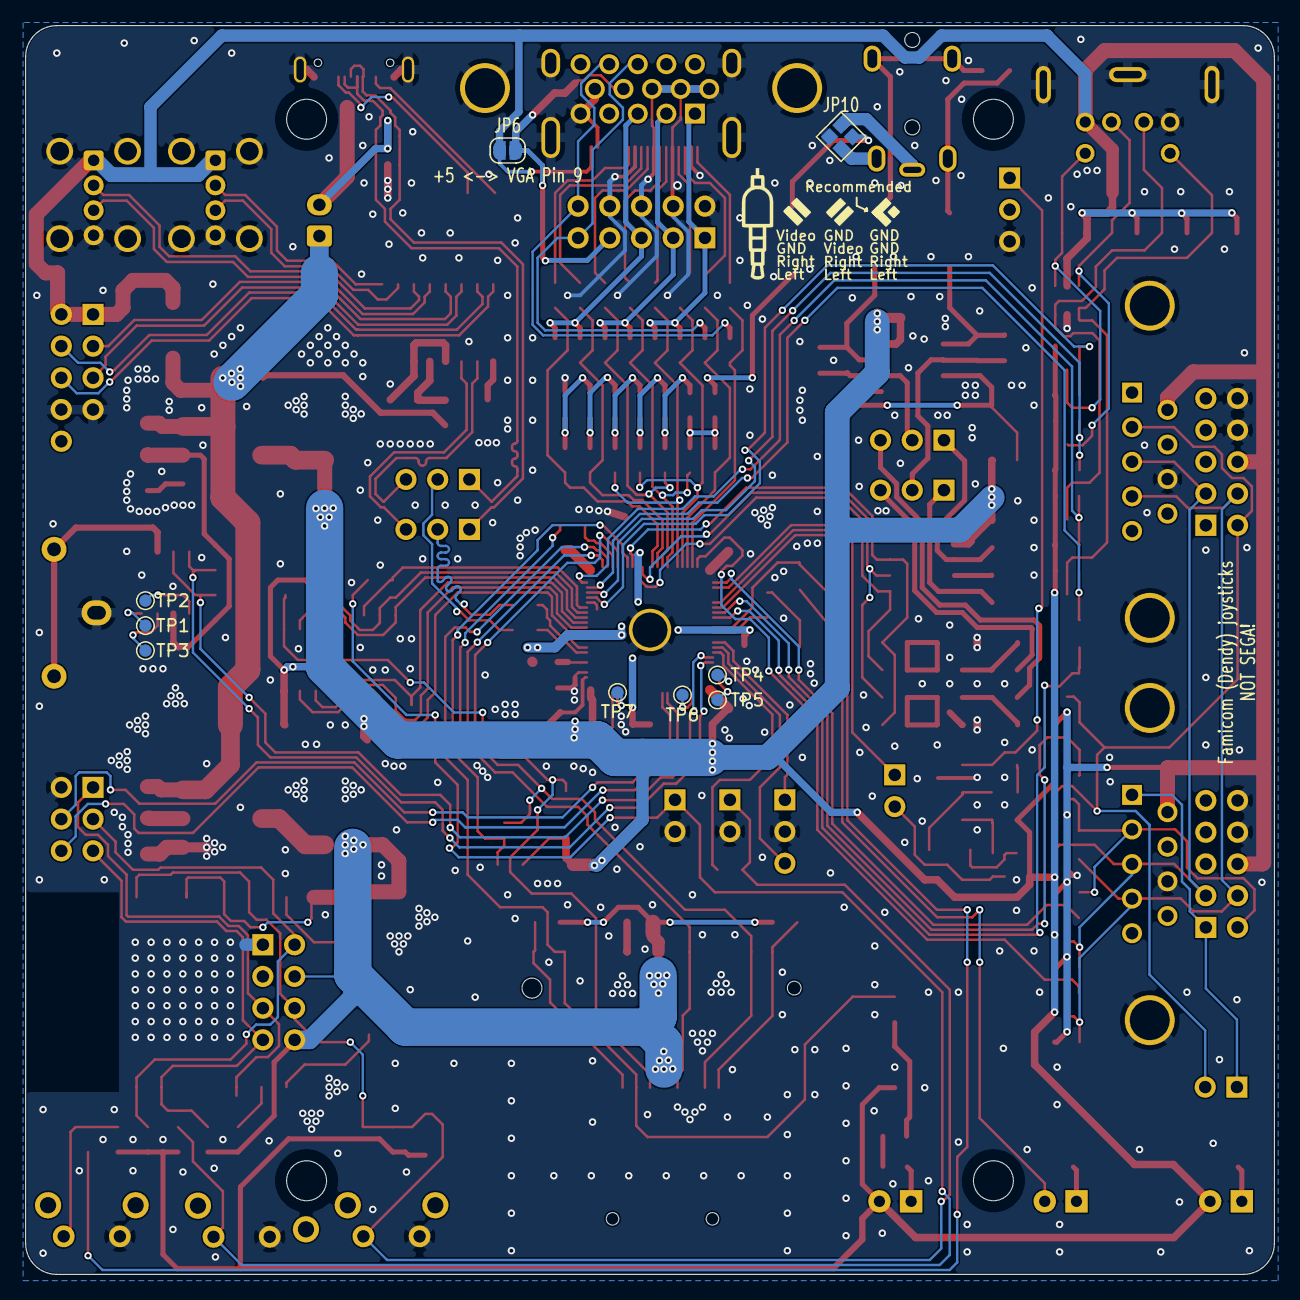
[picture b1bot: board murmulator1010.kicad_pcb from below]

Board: 2 copper layers, 100.0 x 100.0 mm, 222 parts (9 on the bottom side), 153 nets.
